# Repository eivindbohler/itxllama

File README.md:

# ITX-Llama User's Guide
  
> **Note**  
> This document is still a work in progress.  
For feedback, suggestions, etc. - please add a post to the [Vogons thread][vogons-thread].

### Contents
- [Building your own](building.md)
- [Installing the SOM](#installing-the-som)
- [Jumper Configuration](#jumper-configuration)
  * [PS/2 and USB HID](#ps2-or-usb-hid)
  * [Line In](#line-in)
  * [Pi or Wavetable](#pi-or-wavetable)
- [Flashing the BIOS](#flashing-the-bios)
- [DOS](#dos)
  * [Mouse in DOS](#mouse-in-dos)
  * [Audio in DOS](#audio-in-dos)
- [Windows 98](#windows-98)
- [Windows 98 Drivers](#windows-98-drivers)
  * [TBPlus](#tbplus)
  * [USB](#usb)
  * [Crystal Audio](#crystal-audio)
  * [Ethernet](#ethernet)
- [Fans](#fans)
- [mt32-pi](#mt32-pi)

## Installing the SOM
When installing the Vortex86EX SOM, _carefully_ align the module as shown in the image below, and _gently_ push it down on the 64 pins.  
Note that the pins on the motherboard are quite thin and fragile, and if you misalign the SOM or use excessive force, they'll likely bend or break.  
Take your time, be careful and double-check the placement before proceeding further!

## Jumper Configuration
The board should come preinstalled with all the jumpers necessary.  
For changing the configuration, here's a quick walkthrough of the different jumpers and their functionality.

### PS/2 or USB HID
Jumpers: J7, J12, J15, J16

If you want to use a real PS/2 keyboard connected to the purple PS/2 port, place the two topmost jumpers (J15 and J16) to the leftmost position ("PS/2"). For USB HID keyboard connected to one of the white USB ports (between the PS/2 and serial port), place the jumpers to the rightmost side ("USB").  
Same goes for PS/2 mouse and jumpers J7 and J12.

### Line In
Jumpers: J39, J40

If you want to use an external audio source connected to the blue 3.5mm jack port, place both jumpers to the leftmost position ("EXT").  
For using a Raspberry Pi Zero2 or Wavetable board as line-in to the sound card, place the two jumpers to the rightmost position ("INT").

### Pi or Wavetable
Jumpers: J25, J26, J27

For using a Raspberry Pi (Zero2, 3 or 4) for converting MIDI to analog audio, place the three jumpers to the rightmost position ("PI").  
For using a wavetable board, place the jumpers to the leftmost position ("WT").

## Flashing the BIOS
If you've purchased the Vortex86EX system-on-module (SOM) from DMP, ICOP, etc - you need to flash the BIOS first.  
Since the BIOS that comes pre-installed on the SOM is set up for another pinout/configuration, the microSD card slot isn't availble yet, and you need to use a USB flash drive for this part.  
  
Format the flash drive with a DOS-bootable FAT16/32 partition and copy over the [ANYBIOS.EXE and ITXBIOS.ROM files](INITBIOS).  
Alternatively (and easier), just do a block-level transfer of the [INITBIOS.IMG](INITBIOS) file to the flash drive using [Balena Etcher][balena-etcher], `dd` or something similar.  
Then place the flash drive in one of the USB ports (the ones below the RJ45 port). Plug a USB keyboard in the other port. **Note**: at this point, a keyboard plugged into one of the two _HID-only (white)_ ports won't work, you need to use the ones below the RJ45 port!  
Power up the system, and hopefully you'll get a DOS prompt. From there just type:
```
anybios w itxbios.rom
```
Once done, shut down the computer, remove the flash drive and move the keyboard to one of the HID ports.

## DOS
Follow these instructions to set up DOS on a microSD card, SATA drive or USB flash drive:  
(Note: a SATA drive is faster, but this isn't that important in DOS. I recommend using a microSD card, because you'll be able to use the "clicker" feature to simulate the seeking sounds of an old spinning drive, if you're interested in that)
1. Turn off the system, insert a drive of choice.
2. Boot the system, press ESC to bring up the boot menu.
3. Choose the Virtual Floppy drive.
4. Run `fdisk`, select and partition the drive however you want. Make sure to have at least one primary partition, and make it `Active`.
5. Quit fdisk and reboot the system.
6. Once again, boot the system using the Virtual Floppy drive.
7. Run `fdisk /mbr` to write the correct MBR bytes to the new drive.
8. Run `format c: /s` to format the new drive and copy over the necessary system files.
9. Shut down the machine and remove the drive.
10. Copy over DOS and whatever else you want from a modern computer.

### Mouse in DOS
Use [CuteMouse (CTMOUSE.EXE)](DOS-utils).

### Audio in DOS
The Crystal CS4237B sound chip is automatically initialized and configured from the BIOS, so you don't need any drivers in DOS.  
If you wish to change any of the mixer settings, use [CWDMIX.EXE](DOS-Utils).

## Windows 98
Before proceeding, I'd _strongly_ recommend using a SATA drive for Windows 98, as the performance is noticably better than running from an SD card or USB drive.  
  
Download Windows 98 SE from [WinWorldPC][winworldpc-win98]. Product keys are there as well.  
  
Prepare a bootable DOS drive (see the [DOS](#dos) section above), copy the `WIN98` folder over to the drive and run the `SETUP.EXE` from within.

Note: at some point during the installation, you'll get a crash. This is due to the IDE driver being incompatible with the Vortex86EX's IDE controller.  
Reboot, and choose "Safe Mode". From within Win98, install the [TBPLUS](WIN98-drivers/TBPLUS) drivers from R. Loew and then reboot again and complete the installation.  
  
An easier way is to install Windows 98 SE is using a [version I've prepared](WIN98) which has the IDE drivers "slipstreamed" (meaning that Windows will use the updated drivers automatically).

## Windows 98 Drivers

### TBPlus
If you installed the TBPlus drivers during the Windows 98 installation, or used the slipstreamed Windows 98 installer you're all set. If not, install the [TBPlus drivers](WIN98-drivers/TBPLUS).

### USB
In the BIOS Settings, you can choose to have USB flash drives appear to the system as fixed disks.  
With this setting enabled, they'll show up as regular hard drives in DOS and Windows.  
If you turn this setting _off_, you can use flash drives as removable storage in Windows 98. Use [nusb36e.exe](WIN98-drivers/USB) to install the required drivers.

### Crystal Audio
Run `SETUP.EXE` from the [Crystal Audio](WIN98-drivers/CWD-v286-1998-itx-llama) driver folder.

### Ethernet
From Device Manager, find the Ethernet device and install the [RDC R6040 driver](WIN98-drivers/r6040_win98).

## Fans
The Vortex86EX SOM doesn't draw much power, and shouldn't require active cooling if running at or below 300 MHz.  
If you do wish to add one or more fans, the motherboard has three separately controllable 4-pin PWM fan connectors:

Simply connect a modern 4-pin fan to one of these headers, and set the corresponding jumper to either 5V or 12V:

Note: Take care **not** to supply 12V to a 5V fan - you'll likely fry it.

## mt32-pi
If you want to use a Raspberry Pi as an MT-32 or MIDI synthesizer, download and install the [mt32-pi][mt32-pi] bare-metal software on the Pi, and plug it into the motherboard.  
If you go with a Pi Zero 2 (the easiest and cheapest option), make sure to solder the 40-pin connector to the _bottom_ side of the Pi, as seen here:

Look at the [mt32-pi github page][mt32-pi] for setup, configuration options etc.  
As a minimum, you want to set the output of the mt32-pi as type "i2s":
```
output_device = i2s
```  
Use the [mt32-pi-control][mt32-pi-control] software from DOS to switch between MT-32 and MIDI mode.

[balena-etcher]: https://www.balena.io/etcher
[winworldpc-win98]: https://winworldpc.com/download/417d71c2-ae18-c39a-11c3-a4e284a2c3a5
[vogons-thread]: https://www.vogons.org/viewtopic.php?t=93480
[mt32-pi]: https://github.com/dwhinham/mt32-pi
[mt32-pi-control]: https://github.com/gmcn42/mt32-pi-control/tree/main/dos_bin

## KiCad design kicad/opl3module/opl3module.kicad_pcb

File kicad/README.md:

### Notice:
This folder contains all files necessary to produce the ITX-Llama board from JLCPCB, or to continue development of the board.  
However, I don't give any guarantees that everything is correct and working; you need to have a good understanding of Kicad and the PCB/assembly ordering process - and check everything yourself.

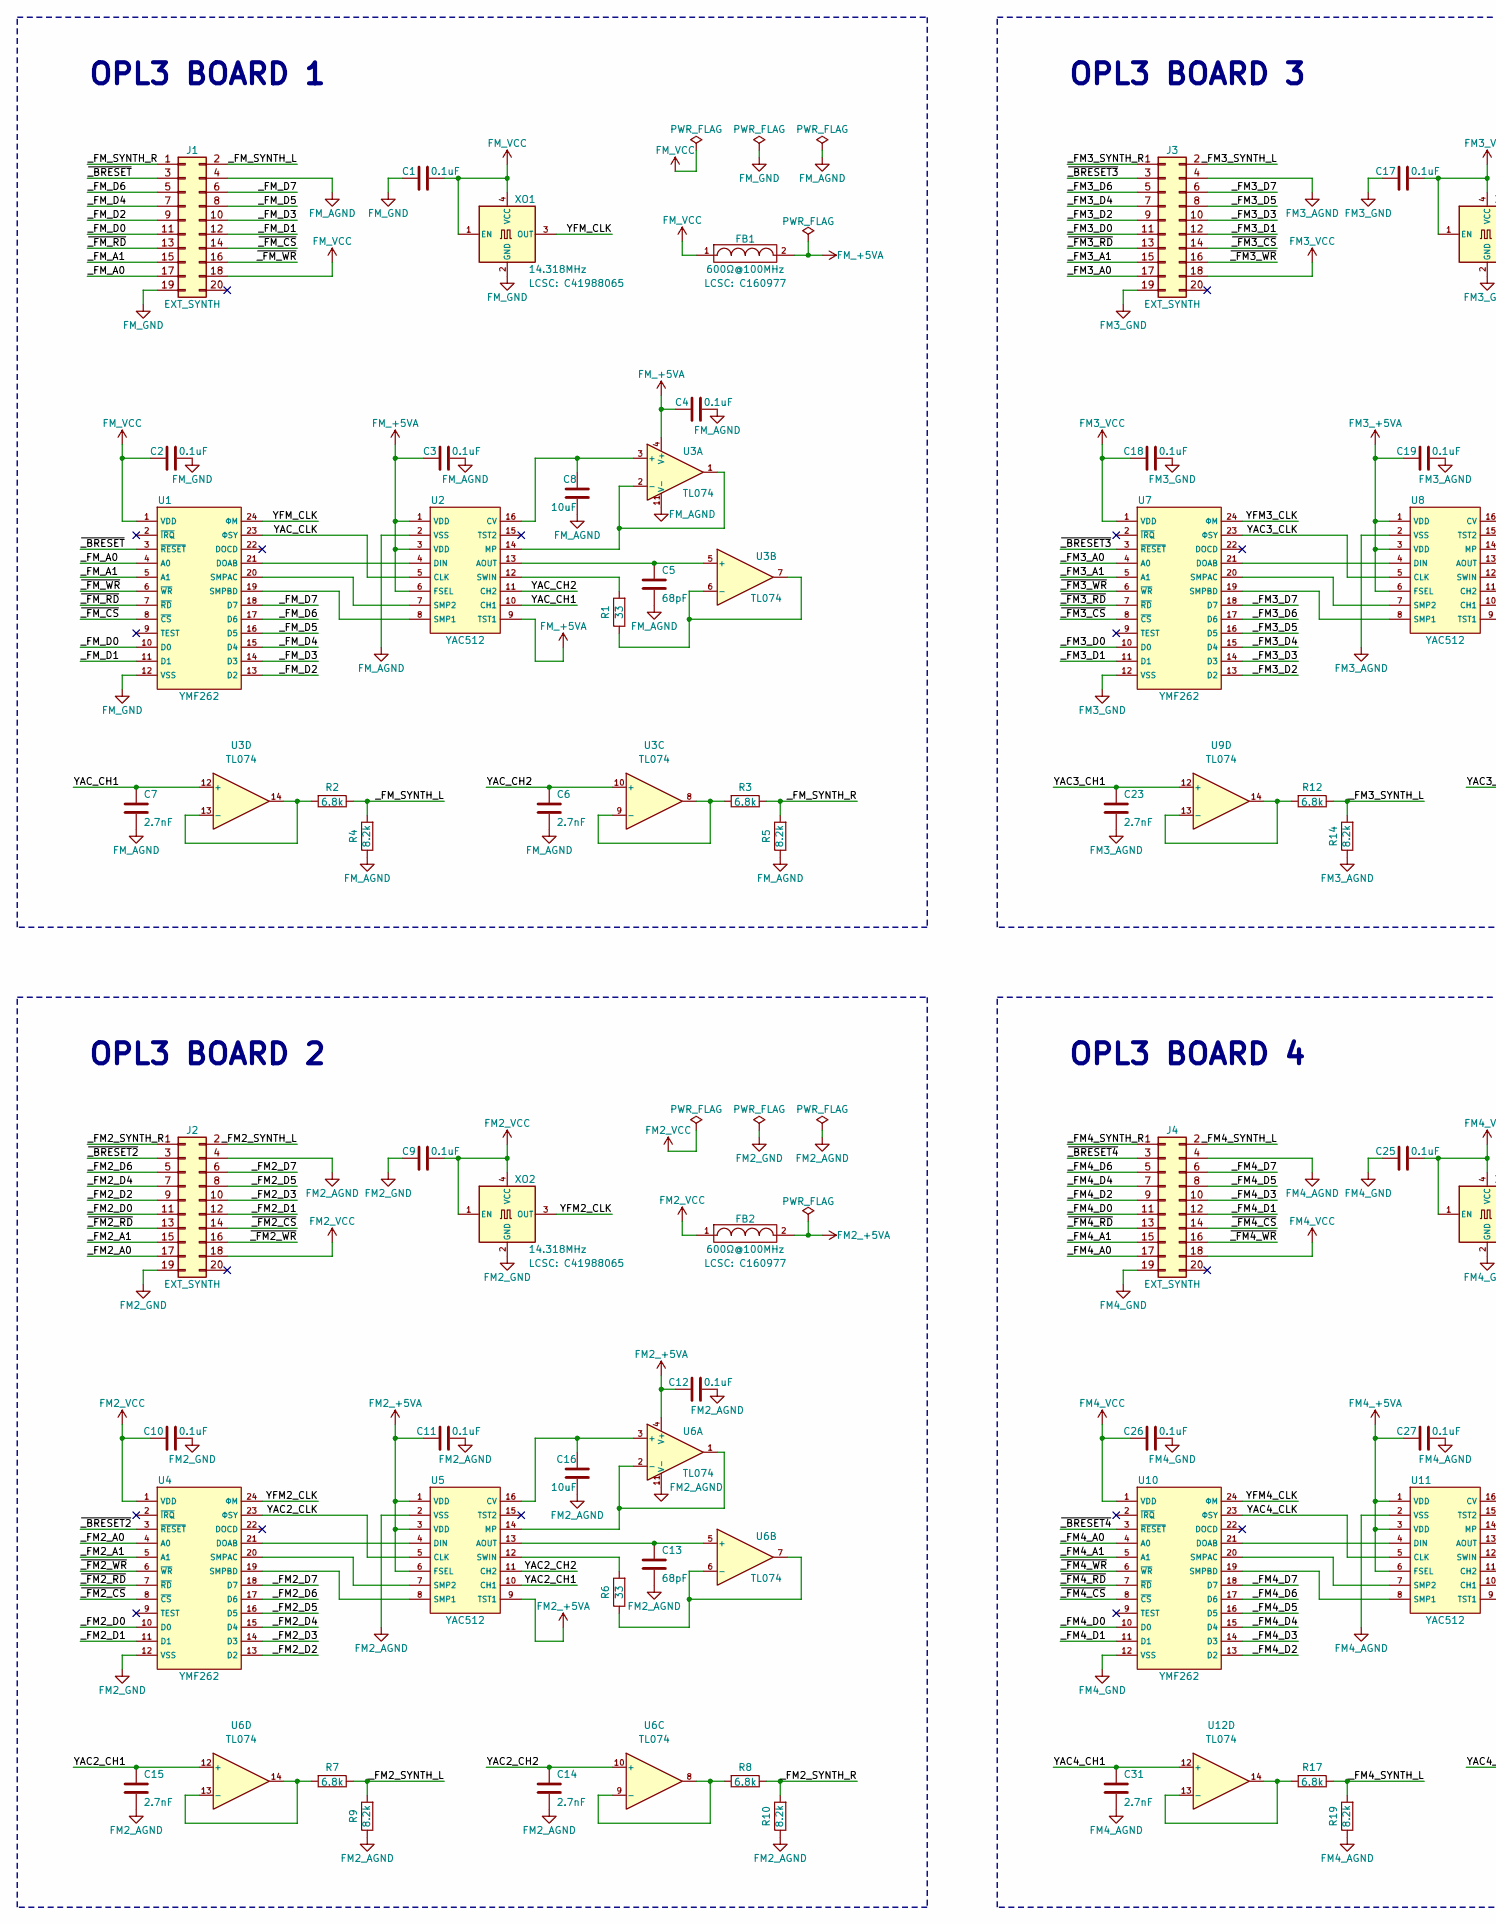
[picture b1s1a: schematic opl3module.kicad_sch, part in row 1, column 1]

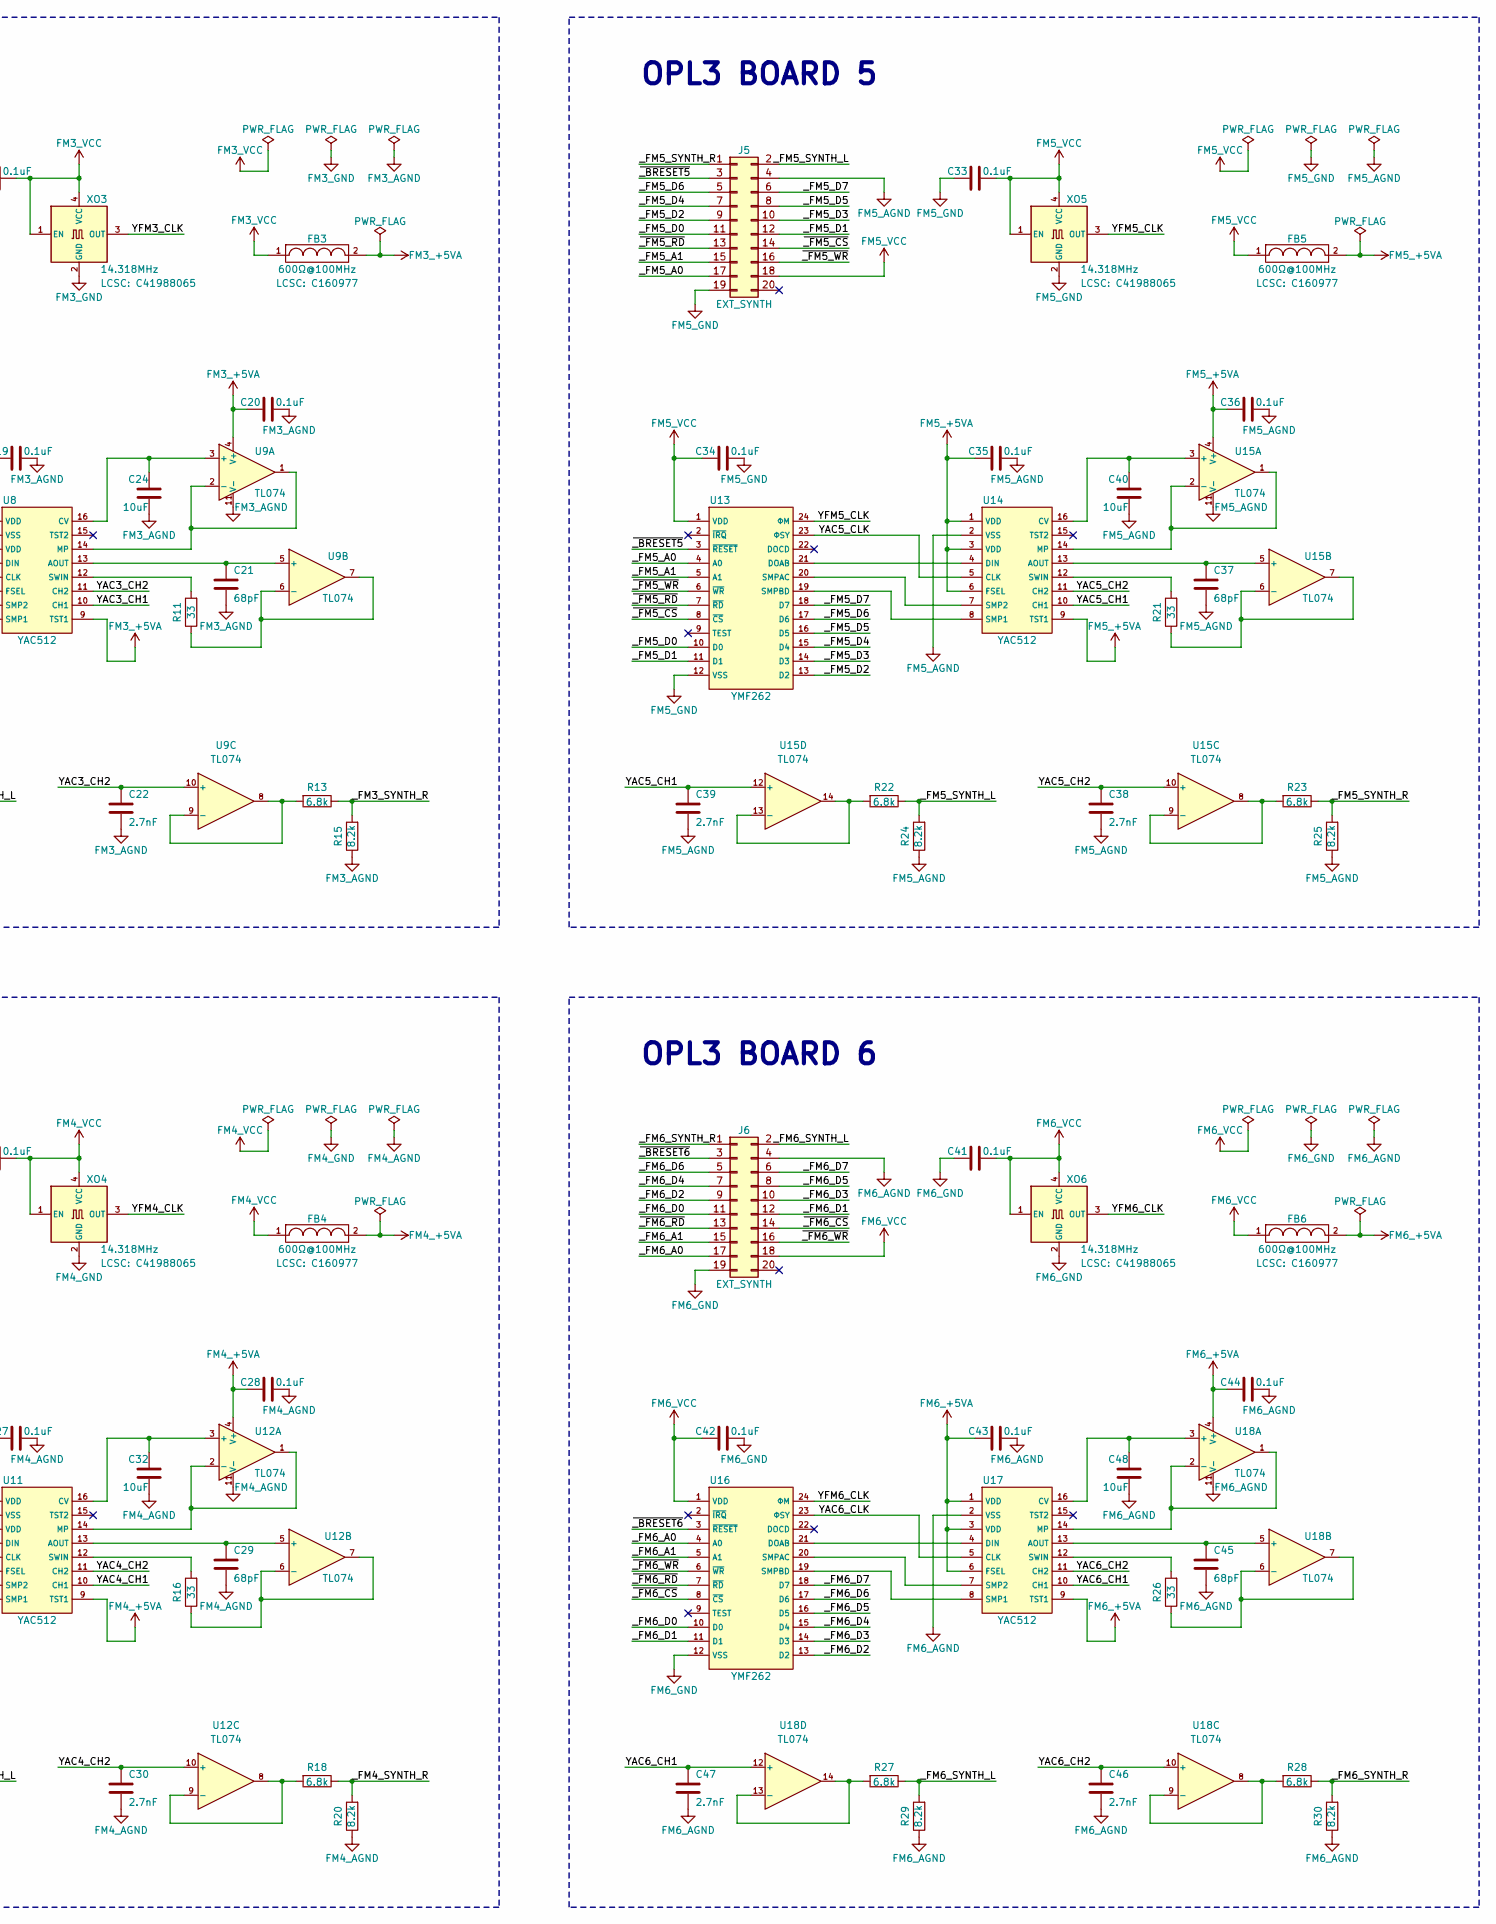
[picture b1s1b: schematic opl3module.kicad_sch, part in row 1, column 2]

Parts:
C1, C2, C3, C4, C9, C10, C11, C12, C17, C18, C19, C20, C25, C26, C27, C28, C33, C34, C35, C36, C41, C42, C43, C44: 0.1uF; C_0402_1005Metric
C5, C13, C21, C29, C37, C45: 68pF; C_0402_1005Metric
C6, C7, C14, C15, C22, C23, C30, C31, C38, C39, C46, C47: 2.7nF; C_0603_1608Metric
C8, C16, C24, C32, C40, C48: 10uF; C_0603_1608Metric
FB1, FB2, FB3, FB4, FB5, FB6: 600Ω@100MHz; R_0402_1005Metric; LCSC C160977
J1, J2, J3, J4, J5, J6: EXT_SYNTH; P_CONN_02X10
R1, R6, R11, R16, R21, R26: 33; R_0402_1005Metric
R2, R3, R7, R8, R12, R13, R17, R18, R22, R23, R27, R28: 6.8k; R_0402_1005Metric
R4, R5, R9, R10, R14, R15, R19, R20, R24, R25, R29, R30: 8.2k; R_0402_1005Metric
U1, U4, U7, U10, U13, U16: YMF262; U_SOP-24_8.4x15.5mm_P1.27mm
U2, U5, U8, U11, U14, U17: YAC512; U_SOP-16_5.3x10.2mm_P1.27mm
U3, U6, U9, U12, U15, U18: TL074; U_SOIC-14_3.9x8.7mm_P1.27mm
XO1, XO2, XO3, XO4, XO5, XO6: 14.318MHz; XO_SMD7050; LCSC C41988065

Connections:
/YAC2_CH1: C15.1, U5.10 (CH1), U6.12 (+)
/YAC2_CH2: C14.1, U5.11 (CH2), U6.10 (+)
/YAC2_CLK: U4.23 (ΦSY), U5.5 (CLK)
/YAC3_CH1: C23.1, U8.10 (CH1), U9.12 (+)
/YAC3_CH2: C22.1, U8.11 (CH2), U9.10 (+)
/YAC3_CLK: U7.23 (ΦSY), U8.5 (CLK)
/YAC4_CH1: C31.1, U11.10 (CH1), U12.12 (+)
/YAC4_CH2: C30.1, U11.11 (CH2), U12.10 (+)
/YAC4_CLK: U10.23 (ΦSY), U11.5 (CLK)
/YAC5_CH1: C39.1, U14.10 (CH1), U15.12 (+)
/YAC5_CH2: C38.1, U14.11 (CH2), U15.10 (+)
/YAC5_CLK: U13.23 (ΦSY), U14.5 (CLK)
/YAC6_CH1: C47.1, U17.10 (CH1), U18.12 (+)
/YAC6_CH2: C46.1, U17.11 (CH2), U18.10 (+)
/YAC6_CLK: U16.23 (ΦSY), U17.5 (CLK)
/YAC_CH1: C7.1, U2.10 (CH1), U3.12 (+)
/YAC_CH2: C6.1, U2.11 (CH2), U3.10 (+)
/YAC_CLK: U1.23 (ΦSY), U2.5 (CLK)
/YFM2_CLK: U4.24 (ΦM), XO2.3 (OUT)
/YFM3_CLK: U7.24 (ΦM), XO3.3 (OUT)
/YFM4_CLK: U10.24 (ΦM), XO4.3 (OUT)
/YFM5_CLK: U13.24 (ΦM), XO5.3 (OUT)
/YFM6_CLK: U16.24 (ΦM), XO6.3 (OUT)
/YFM_CLK: U1.24 (ΦM), XO1.3 (OUT)
/_FM2_A0: J2.17, U4.4 (A0)
/_FM2_A1: J2.15, U4.5 (A1)
/_FM2_D0: J2.11, U4.10 (D0)
/_FM2_D1: J2.12, U4.11 (D1)
/_FM2_D2: J2.9, U4.13 (D2)
/_FM2_D3: J2.10, U4.14 (D3)
/_FM2_D4: J2.7, U4.15 (D4)
/_FM2_D5: J2.8, U4.16 (D5)
/_FM2_D6: J2.5, U4.17 (D6)
/_FM2_D7: J2.6, U4.18 (D7)
/_FM2_SYNTH_L: J2.2, R7.1, R9.2
/_FM2_SYNTH_R: J2.1, R8.1, R10.2
/_FM3_A0: J3.17, U7.4 (A0)
/_FM3_A1: J3.15, U7.5 (A1)
/_FM3_D0: J3.11, U7.10 (D0)
/_FM3_D1: J3.12, U7.11 (D1)
/_FM3_D2: J3.9, U7.13 (D2)
/_FM3_D3: J3.10, U7.14 (D3)
/_FM3_D4: J3.7, U7.15 (D4)
/_FM3_D5: J3.8, U7.16 (D5)
/_FM3_D6: J3.5, U7.17 (D6)
/_FM3_D7: J3.6, U7.18 (D7)
/_FM3_SYNTH_L: J3.2, R12.1, R14.2
/_FM3_SYNTH_R: J3.1, R13.1, R15.2
/_FM4_A0: J4.17, U10.4 (A0)
/_FM4_A1: J4.15, U10.5 (A1)
/_FM4_D0: J4.11, U10.10 (D0)
/_FM4_D1: J4.12, U10.11 (D1)
/_FM4_D2: J4.9, U10.13 (D2)
/_FM4_D3: J4.10, U10.14 (D3)
/_FM4_D4: J4.7, U10.15 (D4)
/_FM4_D5: J4.8, U10.16 (D5)
/_FM4_D6: J4.5, U10.17 (D6)
/_FM4_D7: J4.6, U10.18 (D7)
/_FM4_SYNTH_L: J4.2, R17.1, R19.2
/_FM4_SYNTH_R: J4.1, R18.1, R20.2
/_FM5_A0: J5.17, U13.4 (A0)
/_FM5_A1: J5.15, U13.5 (A1)
/_FM5_D0: J5.11, U13.10 (D0)
/_FM5_D1: J5.12, U13.11 (D1)
/_FM5_D2: J5.9, U13.13 (D2)
/_FM5_D3: J5.10, U13.14 (D3)
/_FM5_D4: J5.7, U13.15 (D4)
/_FM5_D5: J5.8, U13.16 (D5)
/_FM5_D6: J5.5, U13.17 (D6)
/_FM5_D7: J5.6, U13.18 (D7)
/_FM5_SYNTH_L: J5.2, R22.1, R24.2
/_FM5_SYNTH_R: J5.1, R23.1, R25.2
/_FM6_A0: J6.17, U16.4 (A0)
/_FM6_A1: J6.15, U16.5 (A1)
/_FM6_D0: J6.11, U16.10 (D0)
/_FM6_D1: J6.12, U16.11 (D1)
/_FM6_D2: J6.9, U16.13 (D2)
/_FM6_D3: J6.10, U16.14 (D3)
/_FM6_D4: J6.7, U16.15 (D4)
/_FM6_D5: J6.8, U16.16 (D5)
/_FM6_D6: J6.5, U16.17 (D6)
/_FM6_D7: J6.6, U16.18 (D7)
/_FM6_SYNTH_L: J6.2, R27.1, R29.2
/_FM6_SYNTH_R: J6.1, R28.1, R30.2
/_FM_A0: J1.17, U1.4 (A0)
/_FM_A1: J1.15, U1.5 (A1)
/_FM_D0: J1.11, U1.10 (D0)
/_FM_D1: J1.12, U1.11 (D1)
/_FM_D2: J1.9, U1.13 (D2)
/_FM_D3: J1.10, U1.14 (D3)
/_FM_D4: J1.7, U1.15 (D4)
/_FM_D5: J1.8, U1.16 (D5)
/_FM_D6: J1.5, U1.17 (D6)
/_FM_D7: J1.6, U1.18 (D7)
/_FM_SYNTH_L: J1.2, R2.1, R4.2
/_FM_SYNTH_R: J1.1, R3.1, R5.2
/~_BRESET2: J2.3, U4.3 (~RESET)
/~_BRESET3: J3.3, U7.3 (~RESET)
/~_BRESET4: J4.3, U10.3 (~RESET)
/~_BRESET5: J5.3, U13.3 (~RESET)
/~_BRESET6: J6.3, U16.3 (~RESET)
/~_BRESET: J1.3, U1.3 (~RESET)
/~_FM2_CS: J2.14, U4.8 (~CS)
/~_FM2_RD: J2.13, U4.7 (~RD)
/~_FM2_WR: J2.16, U4.6 (~WR)
/~_FM3_CS: J3.14, U7.8 (~CS)
/~_FM3_RD: J3.13, U7.7 (~RD)
/~_FM3_WR: J3.16, U7.6 (~WR)
/~_FM4_CS: J4.14, U10.8 (~CS)
/~_FM4_RD: J4.13, U10.7 (~RD)
/~_FM4_WR: J4.16, U10.6 (~WR)
/~_FM5_CS: J5.14, U13.8 (~CS)
/~_FM5_RD: J5.13, U13.7 (~RD)
/~_FM5_WR: J5.16, U13.6 (~WR)
/~_FM6_CS: J6.14, U16.8 (~CS)
/~_FM6_RD: J6.13, U16.7 (~RD)
/~_FM6_WR: J6.16, U16.6 (~WR)
/~_FM_CS: J1.14, U1.8 (~CS)
/~_FM_RD: J1.13, U1.7 (~RD)
/~_FM_WR: J1.16, U1.6 (~WR)
FM2_+5VA: C11.2, C12.2, FB2.2, U5.1 (VDD), U5.3 (VDD), U5.6 (FSEL), U5.9 (TST1), U6.4 (V+)
FM2_AGND: C11.1, C12.1, C13.2, C14.2, C15.2, C16.1, J2.4, R9.1, R10.1, U5.2 (VSS), U6.11 (V-)
FM2_GND: C9.2, C10.1, J2.19, U4.12 (VSS), XO2.2 (GND)
FM2_VCC: C9.1, C10.2, FB2.1, J2.18, U4.1 (VDD), XO2.1 (EN), XO2.4 (VCC)
FM3_+5VA: C19.2, C20.2, FB3.2, U8.1 (VDD), U8.3 (VDD), U8.6 (FSEL), U8.9 (TST1), U9.4 (V+)
FM3_AGND: C19.1, C20.1, C21.2, C22.2, C23.2, C24.1, J3.4, R14.1, R15.1, U8.2 (VSS), U9.11 (V-)
FM3_GND: C17.2, C18.1, J3.19, U7.12 (VSS), XO3.2 (GND)
FM3_VCC: C17.1, C18.2, FB3.1, J3.18, U7.1 (VDD), XO3.1 (EN), XO3.4 (VCC)
FM4_+5VA: C27.2, C28.2, FB4.2, U11.1 (VDD), U11.3 (VDD), U11.6 (FSEL), U11.9 (TST1), U12.4 (V+)
FM4_AGND: C27.1, C28.1, C29.2, C30.2, C31.2, C32.1, J4.4, R19.1, R20.1, U11.2 (VSS), U12.11 (V-)
FM4_GND: C25.2, C26.1, J4.19, U10.12 (VSS), XO4.2 (GND)
FM4_VCC: C25.1, C26.2, FB4.1, J4.18, U10.1 (VDD), XO4.1 (EN), XO4.4 (VCC)
FM5_+5VA: C35.2, C36.2, FB5.2, U14.1 (VDD), U14.3 (VDD), U14.6 (FSEL), U14.9 (TST1), U15.4 (V+)
FM5_AGND: C35.1, C36.1, C37.2, C38.2, C39.2, C40.1, J5.4, R24.1, R25.1, U14.2 (VSS), U15.11 (V-)
FM5_GND: C33.2, C34.1, J5.19, U13.12 (VSS), XO5.2 (GND)
FM5_VCC: C33.1, C34.2, FB5.1, J5.18, U13.1 (VDD), XO5.1 (EN), XO5.4 (VCC)
FM6_+5VA: C43.2, C44.2, FB6.2, U17.1 (VDD), U17.3 (VDD), U17.6 (FSEL), U17.9 (TST1), U18.4 (V+)
FM6_AGND: C43.1, C44.1, C45.2, C46.2, C47.2, C48.1, J6.4, R29.1, R30.1, U17.2 (VSS), U18.11 (V-)
FM6_GND: C41.2, C42.1, J6.19, U16.12 (VSS), XO6.2 (GND)
FM6_VCC: C41.1, C42.2, FB6.1, J6.18, U16.1 (VDD), XO6.1 (EN), XO6.4 (VCC)
FM_+5VA: C3.2, C4.2, FB1.2, U2.1 (VDD), U2.3 (VDD), U2.6 (FSEL), U2.9 (TST1), U3.4 (V+)
FM_AGND: C3.1, C4.1, C5.2, C6.2, C7.2, C8.1, J1.4, R4.1, R5.1, U2.2 (VSS), U3.11 (V-)
FM_GND: C1.2, C2.1, J1.19, U1.12 (VSS), XO1.2 (GND)
FM_VCC: C1.1, C2.2, FB1.1, J1.18, U1.1 (VDD), XO1.1 (EN), XO1.4 (VCC)
unnamed: U1.21 (DOAB), U2.4 (DIN)
unnamed: U1.20 (SMPAC), U2.7 (SMP2)
unnamed: U1.19 (SMPBD), U2.8 (SMP1)
unnamed: C5.1, U2.13 (AOUT), U3.5 (+)
unnamed: C8.2, U2.16 (CV), U3.3 (+)
unnamed: U2.14 (MP), U3.1, U3.2 (-)
unnamed: R1.2, U2.12 (SWIN)
unnamed: R1.1, U3.6 (-), U3.7
unnamed: R3.2, U3.8, U3.9 (-)
unnamed: R2.2, U3.13 (-), U3.14
unnamed: U4.21 (DOAB), U5.4 (DIN)
unnamed: U4.20 (SMPAC), U5.7 (SMP2)
unnamed: U4.19 (SMPBD), U5.8 (SMP1)
unnamed: C13.1, U5.13 (AOUT), U6.5 (+)
unnamed: C16.2, U5.16 (CV), U6.3 (+)
unnamed: U5.14 (MP), U6.1, U6.2 (-)
unnamed: R6.2, U5.12 (SWIN)
unnamed: R6.1, U6.6 (-), U6.7
unnamed: R8.2, U6.8, U6.9 (-)
unnamed: R7.2, U6.13 (-), U6.14
unnamed: U7.21 (DOAB), U8.4 (DIN)
unnamed: U7.20 (SMPAC), U8.7 (SMP2)
unnamed: U7.19 (SMPBD), U8.8 (SMP1)
unnamed: C21.1, U8.13 (AOUT), U9.5 (+)
unnamed: C24.2, U8.16 (CV), U9.3 (+)
unnamed: U8.14 (MP), U9.1, U9.2 (-)
unnamed: R11.2, U8.12 (SWIN)
unnamed: R11.1, U9.6 (-), U9.7
unnamed: R13.2, U9.8, U9.9 (-)
unnamed: R12.2, U9.13 (-), U9.14
unnamed: U10.21 (DOAB), U11.4 (DIN)
unnamed: U10.20 (SMPAC), U11.7 (SMP2)
unnamed: U10.19 (SMPBD), U11.8 (SMP1)
unnamed: C29.1, U11.13 (AOUT), U12.5 (+)
unnamed: C32.2, U11.16 (CV), U12.3 (+)
unnamed: U11.14 (MP), U12.1, U12.2 (-)
unnamed: R16.2, U11.12 (SWIN)
unnamed: R16.1, U12.6 (-), U12.7
unnamed: R18.2, U12.8, U12.9 (-)
unnamed: R17.2, U12.13 (-), U12.14
unnamed: U13.21 (DOAB), U14.4 (DIN)
unnamed: U13.20 (SMPAC), U14.7 (SMP2)
unnamed: U13.19 (SMPBD), U14.8 (SMP1)
unnamed: C37.1, U14.13 (AOUT), U15.5 (+)
unnamed: C40.2, U14.16 (CV), U15.3 (+)
unnamed: U14.14 (MP), U15.1, U15.2 (-)
unnamed: R21.2, U14.12 (SWIN)
unnamed: R21.1, U15.6 (-), U15.7
unnamed: R23.2, U15.8, U15.9 (-)
unnamed: R22.2, U15.13 (-), U15.14
unnamed: U16.21 (DOAB), U17.4 (DIN)
unnamed: U16.20 (SMPAC), U17.7 (SMP2)
unnamed: U16.19 (SMPBD), U17.8 (SMP1)
unnamed: C45.1, U17.13 (AOUT), U18.5 (+)
unnamed: C48.2, U17.16 (CV), U18.3 (+)
unnamed: U17.14 (MP), U18.1, U18.2 (-)
unnamed: R26.2, U17.12 (SWIN)
unnamed: R26.1, U18.6 (-), U18.7
unnamed: R28.2, U18.8, U18.9 (-)
unnamed: R27.2, U18.13 (-), U18.14

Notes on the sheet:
OPL3 BOARD 3
OPL3 BOARD 1
OPL3 BOARD 2
OPL3 BOARD 5
OPL3 BOARD 4
OPL3 BOARD 6

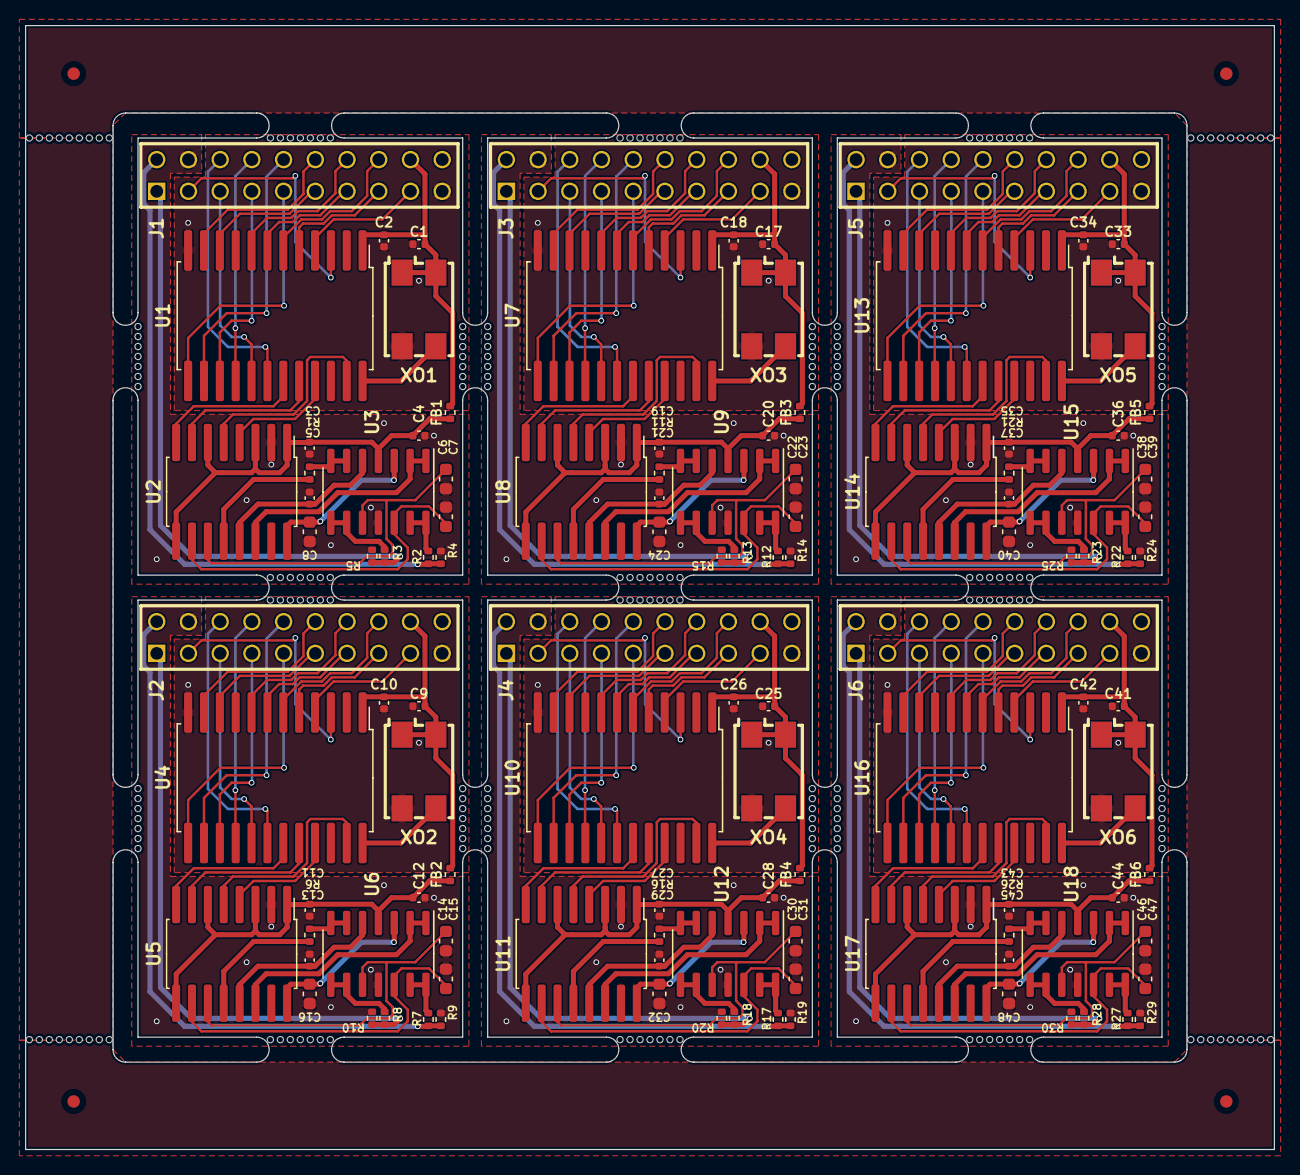
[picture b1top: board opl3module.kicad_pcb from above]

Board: 4 copper layers, 100.0 x 90.0 mm, 114 parts (0 on the bottom side), 204 nets.

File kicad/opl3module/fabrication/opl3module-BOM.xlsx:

Comment | Designator | Footprint | LCSC
0.1uF | C1,C2,C3,C4,C9,C10,C11,C12,C17,C18,C19,C20,C25,C26,C27,C28,C33,C34,C35,C36,C41,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 | C_0402_1005Metric | C1525
68pF | C5,C13,C21,C29,C37,C45 | C_0402_1005Metric | C76977
2.7nF | C6,C7,C14,C15,C22,C23,C30,C31,C38,C39,C46,C47 | C_0603_1608Metric | C1625600
10uF | C8,C16,C24,C32,C40,C48 | C_0603_1608Metric | C344022
600Ω@100MHz | FB1,FB2,FB3,FB4,FB5,FB6 | R_0402_1005Metric | C160977
EXT_SYNTH | J1,J2,J3,J4,J5,J6 | P_CONN_02X10 | C492427
33 | R1,R6,R11,R16,R21,R26 | R_0402_1005Metric | C25105
6.8k | R2,R3,R7,R8,R12,R13,R17,R18,R22,R23,R27,R28 | R_0402_1005Metric | C93940
8.2k | R4,R5,R9,R10,R14,R15,R19,R20,R24,R25,R29,R30 | R_0402_1005Metric | C138071
YMF262 | U1,U4,U7,U10,U13,U16 | U_SOP-24_8.4x15.5mm_P1.27mm | C9900016870
YAC512 | U2,U5,U8,U11,U14,U17 | U_SOP-16_5.3x10.2mm_P1.27mm | C9900130385
TL074 | U3,U6,U9,U12,U15,U18 | U_TSSOP-14_4.4x5mm_P0.65mm | C6964
14.318MHz | XO1,XO2,XO3,XO4,XO5,XO6 | XO_SMD7050 | C41988065

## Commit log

2023-12-06 add anybios.exe
2023-12-06 add win98 drivers
2023-12-06 add fan mount 3d models
2023-12-06 add fan mount description file
2023-12-06 add fan mount image, update description
2023-12-08 update drivers, documentation
2023-12-08 update documentation
2023-12-14 update BIOS
2024-02-07 add kicad project
2024-02-18 Add note about mt32-pi i2s output
2024-05-09 add rp2040 and attiny code
2024-05-10 add opl3 kicad project
2024-05-19 Update platformio.ini
    Adding hfuse lfuse and efuse settings as well as Arduino ISP programming
2024-07-16 add pick and place file
2024-09-25 update readme, bom
2024-09-25 fix broken links
2024-11-01 Add LICENSE
2024-11-13 add rp2040 binary
2024-11-16 integrate ps2x2pico as git submodule
2024-11-16 correct GPIO for USB port
2024-11-20 fix 8bitdo keyboard
2024-11-20 report mode for every device
2024-11-21 NKRO testing
2024-11-27 NKRO implemented
2024-12-05 Bump version: ps2x2pico-2.0
2024-12-15 Bump version: ps2x2pico-2.1
2025-02-27 fix indentation in platform.ini
2025-02-27 improve reliability by adding delays
2025-02-27 add brownout detection to platform.ini
2025-03-13 fix startup issue with PICO_XOSC_STARTUP_DELAY_MULTIPLIER=64
2025-04-20 fix SHIFT not working
2025-04-20 FLASH readme

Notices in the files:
kicad/opl3module/opl3module.kicad_pcb:
Revision 1.0 © 2025
